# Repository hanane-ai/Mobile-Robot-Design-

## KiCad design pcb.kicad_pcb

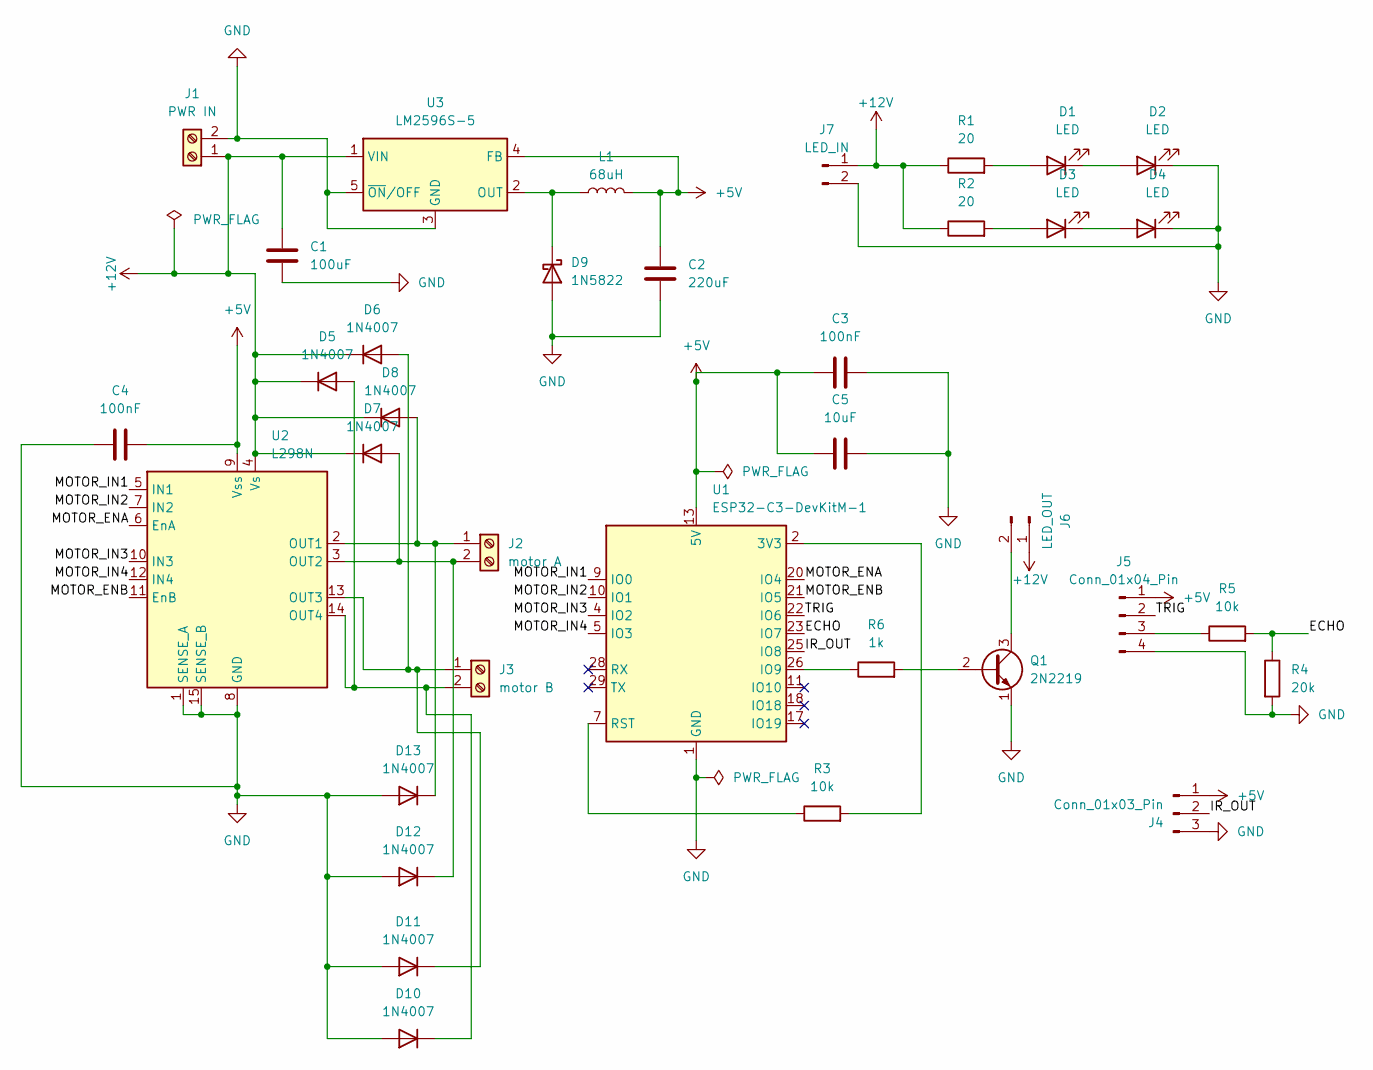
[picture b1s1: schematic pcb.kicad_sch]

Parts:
C1: 100uF; CP_Radial_D8.0mm_P3.50mm
C2: 220uF; C_Radial_D10.0mm_H12.5mm_P5.00mm
C3, C4: 100nF; C_Disc_D5.0mm_W2.5mm_P5.00mm
C5: 10uF; C_Radial_D5.0mm_H5.0mm_P2.00mm
D1, D2, D3, D4: LED; LED_D5.0mm
D5, D6, D7, D8, D10, D11, D12, D13: 1N4007; D_DO-41_SOD81_P10.16mm_Horizontal
D9: 1N5822; D_DO-201AD_P15.24mm_Horizontal
J1: PWR IN; BarrelJack_Horizontal
J2: motor A; PhoenixContact_MC_1,5_2-G-3.5_1x02_P3.50mm_Horizontal
J3: motor B; PhoenixContact_MC_1,5_2-G-3.5_1x02_P3.50mm_Horizontal
J4: Conn_01x03_Pin; PinHeader_1x03_P2.54mm_Vertical
J5: Conn_01x04_Pin; PinHeader_1x04_P2.54mm_Vertical
J6: LED_OUT; PinHeader_1x02_P2.54mm_Vertical_SMD_Pin1Left
J7: LED_IN; PinHeader_1x02_P2.54mm_Vertical_SMD_Pin1Left
L1: 68uH; L_Axial_L5.3mm_D2.2mm_P10.16mm_Horizontal_Vishay_IM-1
Q1: 2N2219; TO-39-3
R1, R2: 20; R_Axial_Power_L25.0mm_W9.0mm_P27.94mm
R3, R5: 10k; R_Axial_DIN0207_L6.3mm_D2.5mm_P10.16mm_Horizontal
R4: 20k; R_Axial_DIN0207_L6.3mm_D2.5mm_P10.16mm_Horizontal
R6: 1k; R_Axial_DIN0207_L6.3mm_D2.5mm_P7.62mm_Horizontal
U1: ESP32-C3-DevKitM-1
U2: L298N; TO-220-15_P2.54x5.08mm_StaggerOdd_Lead4.58mm_Vertical
U3: LM2596S-5; TO-263-5_TabPin3

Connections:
+5V: C2.1, C3.1, C4.2, C5.1, J4.1, J5.1, L1.2, U1.13 (5V), U1.14 (5V), U2.9 (Vss), U3.4 (FB)
+12V: C1.2, D5.1 (K), D6.1 (K), D7.1 (K), D8.1 (K), J1.1, J6.1, J7.1, R1.1, R2.1, U2.4 (Vs), U3.1 (VIN)
/ECHO: R4.1, R5.2, U1.23 (IO7)
/IR_OUT: J4.2, U1.25 (IO8)
/MOTOR_ENA: U1.20 (IO4), U2.6 (EnA)
/MOTOR_ENB: U1.21 (IO5), U2.11 (EnB)
/MOTOR_IN1: U1.9 (IO0), U2.5 (IN1)
/MOTOR_IN2: U1.10 (IO1), U2.7 (IN2)
/MOTOR_IN3: U1.4 (IO2), U2.10 (IN3)
/MOTOR_IN4: U1.5 (IO3), U2.12 (IN4)
/TRIG: J5.2, U1.22 (IO6)
GND: C1.1, C2.2, C3.2, C4.1, C5.2, D2.1 (K), D4.1 (K), D9.2 (A), D10.2 (A), D11.2 (A), D12.2 (A), D13.2 (A), J1.2, J4.3, J5.4, J7.2, Q1.1 (E), R4.2, U1.1 (GND), U1.6 (GND), U1.8 (GND), U1.12 (GND), U1.15 (GND), U1.16 (GND), U1.19 (GND), U1.24 (GND), U1.27 (GND), U1.30 (GND), U2.1 (SENSE_A), U2.8 (GND), U2.15 (SENSE_B), U3.3 (GND), U3.5 (~ON/OFF)
unnamed: D1.2 (A), R1.2
unnamed: D1.1 (K), D2.2 (A)
unnamed: D3.2 (A), R2.2
unnamed: D3.1 (K), D4.2 (A)
unnamed: D9.1 (K), L1.1, U3.2 (OUT)
unnamed: D5.2 (A), D10.1 (K), J3.2, U2.14 (OUT4)
unnamed: D6.2 (A), D11.1 (K), J3.1, U2.13 (OUT3)
unnamed: D7.2 (A), D12.1 (K), J2.2, U2.3 (OUT2)
unnamed: D8.2 (A), D13.1 (K), J2.1, U2.2 (OUT1)
unnamed: J5.3, R5.1
unnamed: J6.2, Q1.3 (C)
unnamed: Q1.2 (B), R6.2
unnamed: R3.2, U1.2 (3V3), U1.3 (3V3)
unnamed: R6.1, U1.26 (IO9)
unnamed: R3.1, U1.7 (RST)

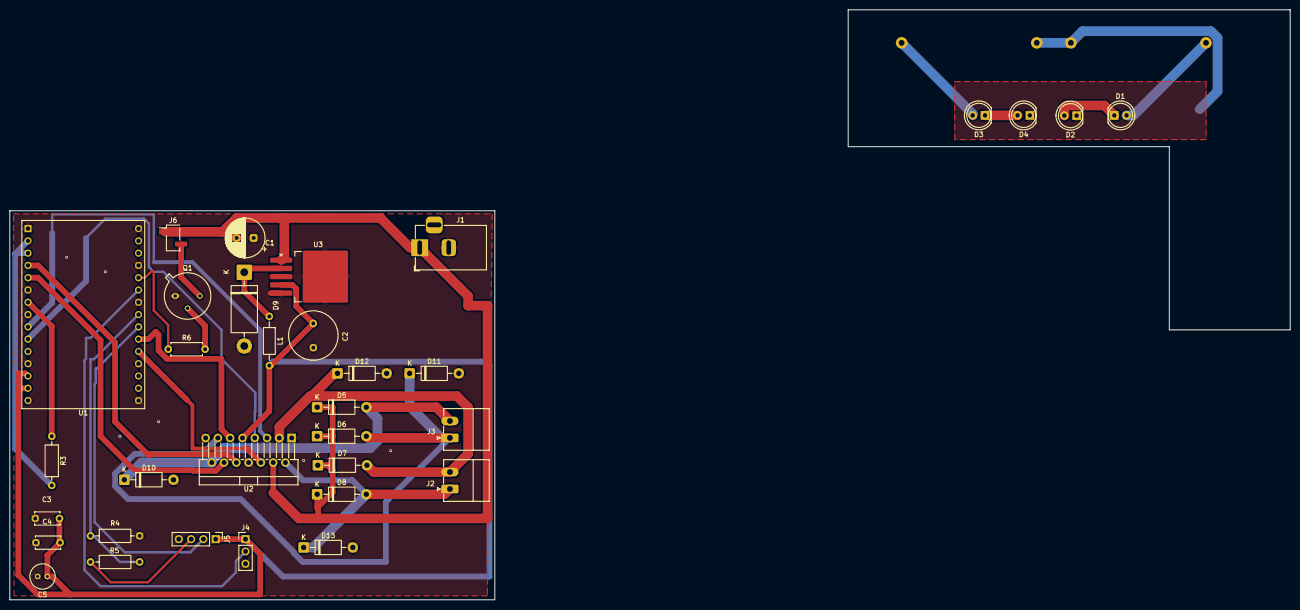
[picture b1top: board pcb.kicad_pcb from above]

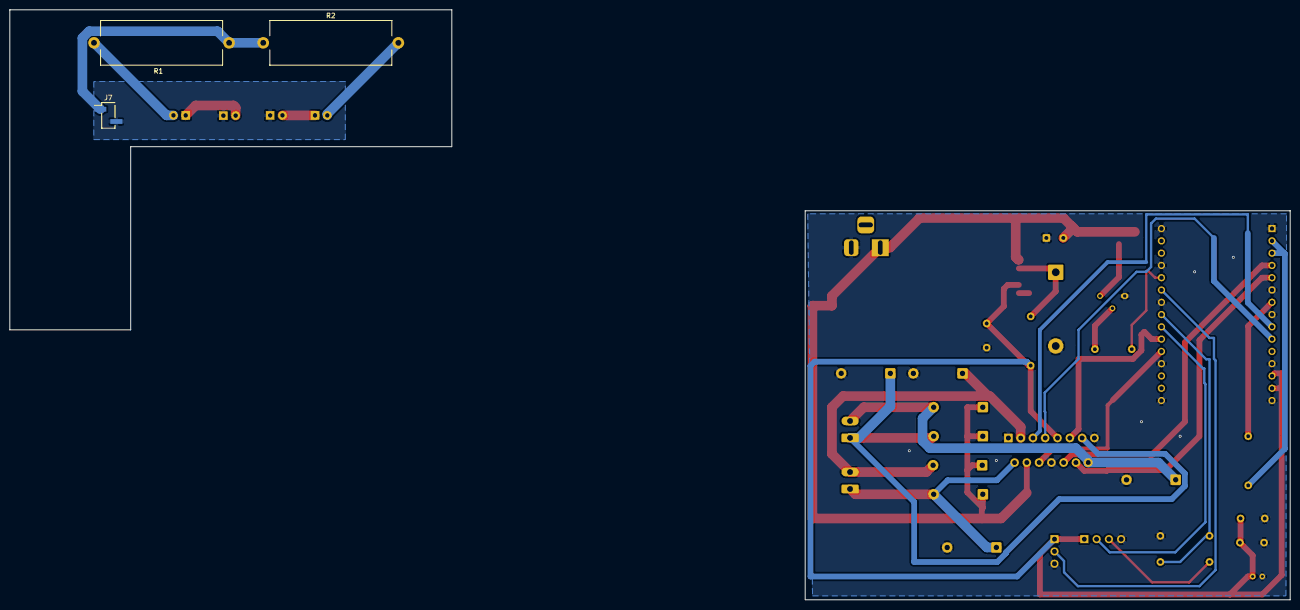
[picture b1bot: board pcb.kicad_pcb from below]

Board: 2 copper layers, 100.3 x 80.4 mm, 36 parts (3 on the bottom side), 27 nets.

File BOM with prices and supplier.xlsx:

Bill of Materials (BOM)
Reference | Qty | Value | Price | supplier
C1 | 1 | 100uF | 10 | link
C2 | 1 | 220uF
C3, C4 | 2 | 100nF
C5 | 1 | 10uF
D1-D4 | 4 | LED | 0.45 | link
D5-D8, D10-D13 | 8 | 1N4007 | 2.68 | link
D9 | 1 | 1N5822
J1 | 1 | PWR IN | 3.06 | link
J2 | 1 | motor A | 0.6 | link
J3 | 1 | motor B | 0.6 | link
J4 | 1 | Conn_01x03_Pin | 0.59 | link
J5 | 1 | Conn_01x04_Pin | 13.24 | link
J6 | 1 | LED_OUT | 0.43 | link
J7 | 1 | LED_IN | 0.43 | link
L1 | 1 | 68uH | 5.96 | link
Q1 | 1 | 2N2219 | 6 | link
R1, R2 | 2 | 20 ohm | 13.33 | link
R3, R5 | 2 | 10k ohm
R4 | 1 | 20k ohm
R6 | 1 | 1k ohm
U1 | 1 | ESP32-C3-DevKitM-1 | 2.8 | link
U2 | 1 | L298N | 1.1299999999999999 | link
U3 | 1 | LM2596S-5 | 2.33 | link
Total | 36 |  | 63.629999999999995

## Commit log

2026-04-02 Create Costs
2026-04-02 Rename Costs to Costs.md
2026-04-19 Design Calculations
